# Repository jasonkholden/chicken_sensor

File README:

This is a 4-input temperature sensor daughter board for the ESP8266

A detailed project writeup is available at [Making Electronics](http://makingelectronics.com/?q=node/3)

This daughter board will multiplex up to 4 10k thermistor inputs to the
ADC of the ESP8266.  Form factor targets the Adafruit HUZZAH ESP8266 Breakout

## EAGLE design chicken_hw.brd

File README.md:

#4-Input Temperature Sensor Daughter Board

This is a 4-input temperature sensor daughter board for the ESP8266

A detailed project writeup is available at [Making Electronics](http://makingelectronics.com/?q=node/3) on how to use this board to build a solar-powered IoT Temperature sensor

This daughter board will multiplex up to 4 10k thermistor inputs to the
1V-max ADC of the ESP8266.  The current form factor targets the Adafruit HUZZAH ESP8266 Breakout footprint

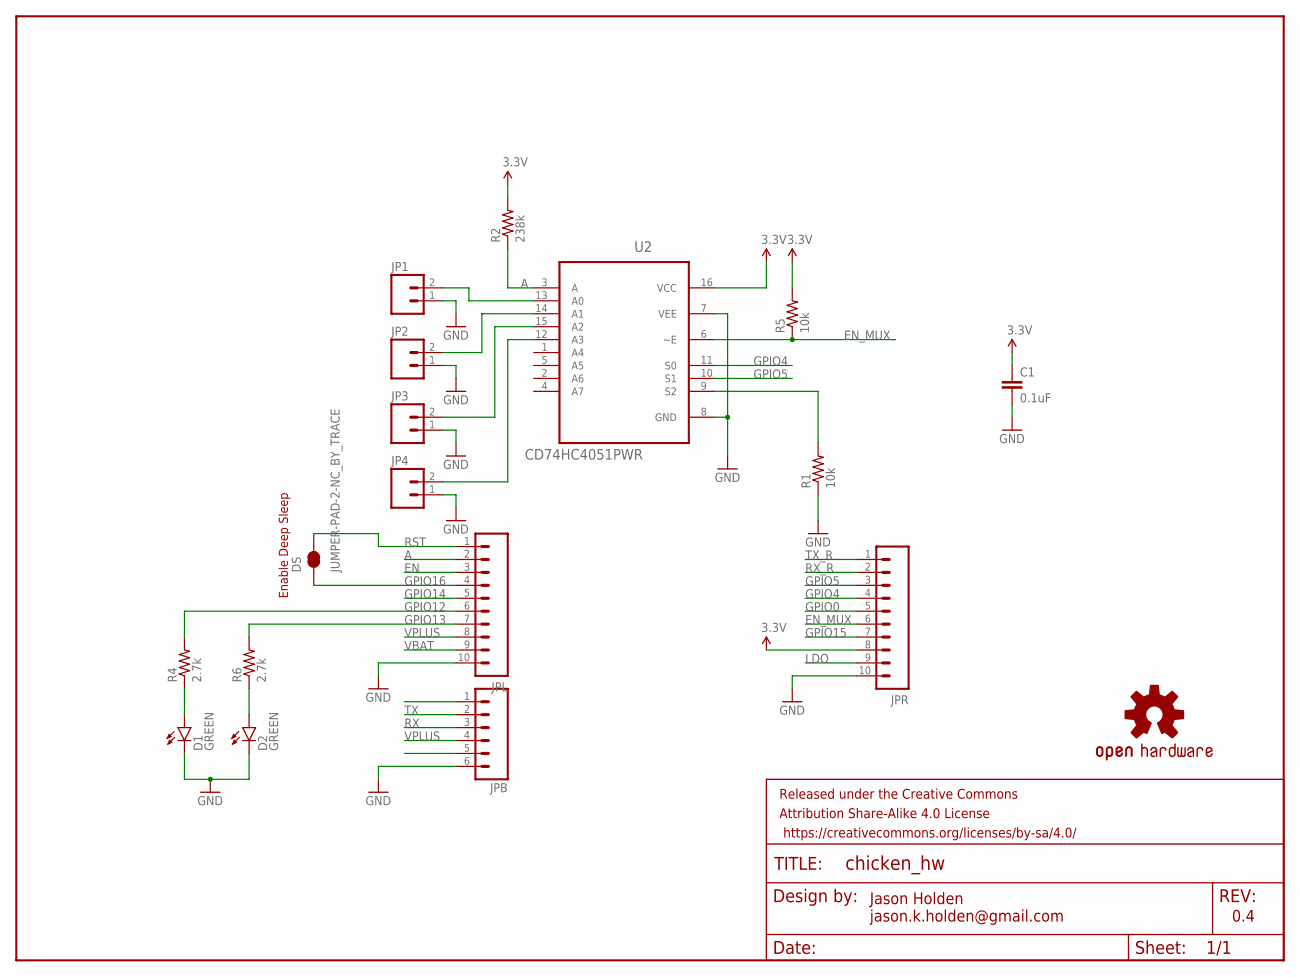
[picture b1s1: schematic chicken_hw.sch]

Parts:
C1: 0.1uF; 0603-CAP
D1, D2: GREEN; LED-0603
DS: JUMPER-PAD-2-NC_BY_TRACE; PAD-JUMPER-2-NC_BY_TRACE_YES_SILK
FRAME1: FRAME-LETTER; CREATIVE_COMMONS
JP1, JP2, JP3, JP4: M02PTH; 1X02
JPB: M06SILK_FEMALE_PTH; 1X06
JPL: M10SILK_FEMALE_PTH; 1X10
JPR: M10SILK_FEMALE_PTH; 1X10
LOGO1: OSHW-LOGOS; OSHW-LOGO-S
R1, R5: 10k; 0603-RES
R2: 238k; 0603-RES
R4, R6: 2.7k; 0603-RES
U2: CD74HC4051PWR; SOP65P640X120-16N

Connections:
3.3V: C1.1, JPR.8, R2.2, R5.2, U2.16 (VCC)
A: JPL.2, R2.1, U2.3 (A)
EN: JPL.3
EN_MUX: JPR.6, R5.1, U2.6 (~E)
GND: C1.2, D1.C, D2.C, JP1.1, JP2.1, JP3.1, JP4.1, JPB.6, JPL.10, JPR.10, R1.1, U2.7 (VEE), U2.8 (GND)
GPIO0: JPR.5
GPIO4: JPR.4, U2.11 (S0)
GPIO5: JPR.3, U2.10 (S1)
GPIO12: JPL.6, R4.2
GPIO13: JPL.7, R6.2
GPIO14: JPL.5
GPIO15: JPR.7
GPIO16: DS.1, JPL.4
LDO: JPR.9
unnamed: R1.2, U2.9 (S2)
unnamed: JP1.2, U2.13 (A0)
unnamed: JP2.2, U2.14 (A1)
unnamed: JP3.2, U2.15 (A2)
unnamed: JP4.2, U2.12 (A3)
unnamed: D1.A, R4.1
unnamed: D2.A, R6.1
RST: DS.2, JPL.1
RX: JPB.3
RX_R: JPR.2
TX: JPB.2
TX_R: JPR.1
VBAT: JPL.9
VPLUS: JPB.4, JPL.8

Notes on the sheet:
Jason Holden jason.k.holden@gmail.com
Enable Deep Sleep
0.4

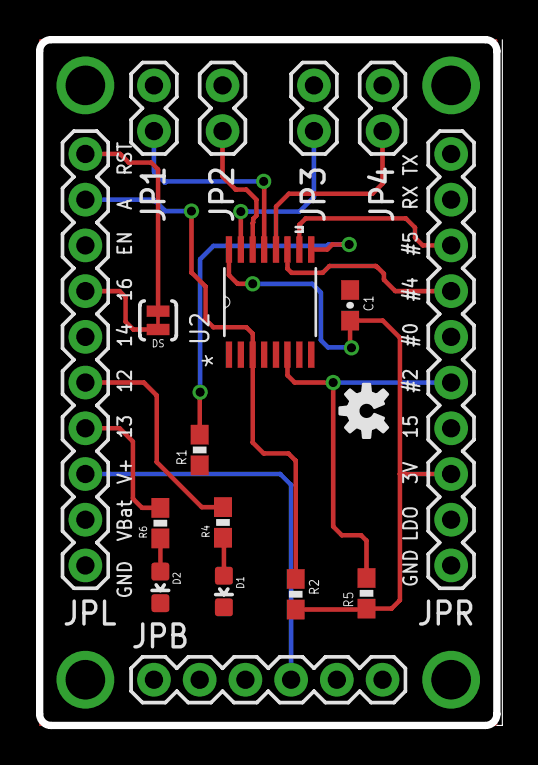
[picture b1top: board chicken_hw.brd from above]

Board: 2 copper layers, 25.5 x 38.1 mm, 19 parts (0 on the bottom side), 18 nets.

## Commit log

2015-11-07 Initial project setup for a chicken coop temperature sensor
2015-11-07 Add nets and connectors for breakout board for Adafruit HUZZAH ESP8266
2015-11-07 Start adding analog mux to design
2015-11-08 Rough placement of components on board design
2015-11-08 Add connector text to board design
2015-11-08 Final initial placement of components, ready for autorouting
2015-11-08 Improve lettering thickness on SMT parts
2015-11-08 Bevel edges of dimensions layer
2015-11-08 First complete routing of board, 2 vias
2015-11-08 Add digikey bom for SMT parts
2015-11-08 Add to bom a DC power jack compatible with solar power supply
2015-11-08 Add two leds to gpio 16,14 for easy status
2015-11-08 Finish touchup of autorouter traces manually
2015-11-08 Update BOM with LED and led resistors
2015-11-08 Add designer information and schematic frame
2015-11-08 Change license prior to first release of code to CC BY-SA 4.0
    License for hardware designs should be compatible with the Sparkfun
    libraries that are utilized by this project
2015-11-08 Add open source hardware logo and bottom silk
2015-11-08 Add ver0.1 gerbers ready for OSH Park to fabricate
2015-11-08 Add connectors to BOM
2015-11-08 Replace dc jack in BOM since current part selection was out of stock
    New part is slightly more expensive
2015-11-08 Add project README file
2015-11-08 Add bom for adafruit
2015-11-15 Enable ESP8266 deepsleep by connecting GPIO16 to RESET - bump to ver 0.2
    Remove led's on GPIO 16,14 and move them to GPIO 12, 13
2015-11-15 Add gerbers submitted to OSH Park on 11/15/2015
2015-11-15 Replace connector. Previous connector didn't mate with solar panel
2015-11-15 Revert "Replace connector. Previous connector didn't mate with solar panel"
    This reverts commit 5334f3598c814a8855e17c09d457e76b308023c7.
    Parts do indeed mate, the fit is just _very_ tight. Since the hi-current
    part is readily available on digikey, go back to it, even though its a little
    more expensive. Either part will work going forward though.
2015-11-30 Fix bom to use 0603 237k reistor, not 0805
2015-12-14 Switch to 8to1 mux to save on cost
2015-12-14 Fully routed 8:1 mux, ready for production
2015-12-14 Add gerbers submitted to OSH Park on 12/13/2015
2015-12-14 Add BOM for 0.3 board
2015-12-20 Add link to project writeup in readme file
2015-12-20 More markdown updates to readme file
2015-12-20 Move readme to markdown file
2015-12-20 Include screenshot of latest board in readme
2016-01-03 Fix ERC errors w/ V0.3 board VCC and S2 not connected (unrouted)
2016-01-03 Route missing signals for mux from 12c953b27b064bb54cf89404
2016-01-03 Rev silkscreen to ver 0.4
2016-01-03 Control v0.4 gerber files submitted to OSHPark for fabrication

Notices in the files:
parts and their libraries:
SparkFun-Connectors: Licensing: Creative Commons ShareAlike 4.0 International - https://creativecommons.org/licenses/by-sa/4.0
SparkFun-Aesthetics: Released under the Creative Commons Attribution Share-Alike 4.0 License
SparkFun-Aesthetics: https://creativecommons.org/licenses/by-sa/4.0
